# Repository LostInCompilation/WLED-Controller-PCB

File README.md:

# WLED Controller (ESP32) - 4 Channels - Current and power monitoring

### ❤️💰 Donation - Help a student pay rent

## You can buy the PCB in my shop
Buy the PCB here (available in 2 days): https://buymeacoffee.com/lostincompilation

## Features
- 4 Channels
    - Max 25A total
    - Max 10A per channel
- Every channel has _independent_ current, power and voltage monitoring (using INA219)
- Sending power monitoring data to HomeAssistant via MQTT
- Relay for cutting power to LED-strips
- Touch surface on PCB (next to LED) usable as custom button
- SMD-1206 parts for easy hand soldering
- Reverse polarity protection
- Seperate 3.3V low noise voltage regulator for audio section
- _**Optional:** INMP441 I2S Microphone with low noise power supply_
- _**Optional:** Line-In Audio with extension board (I2S ADC: PCM1808)_

## Usermod
This board requires a usermod for WLED for full support of all features including power monitoring.

_**NOTE:** The usermod is currently in development and will be uploaded to thtis repository._

## 3D Board view

## Board

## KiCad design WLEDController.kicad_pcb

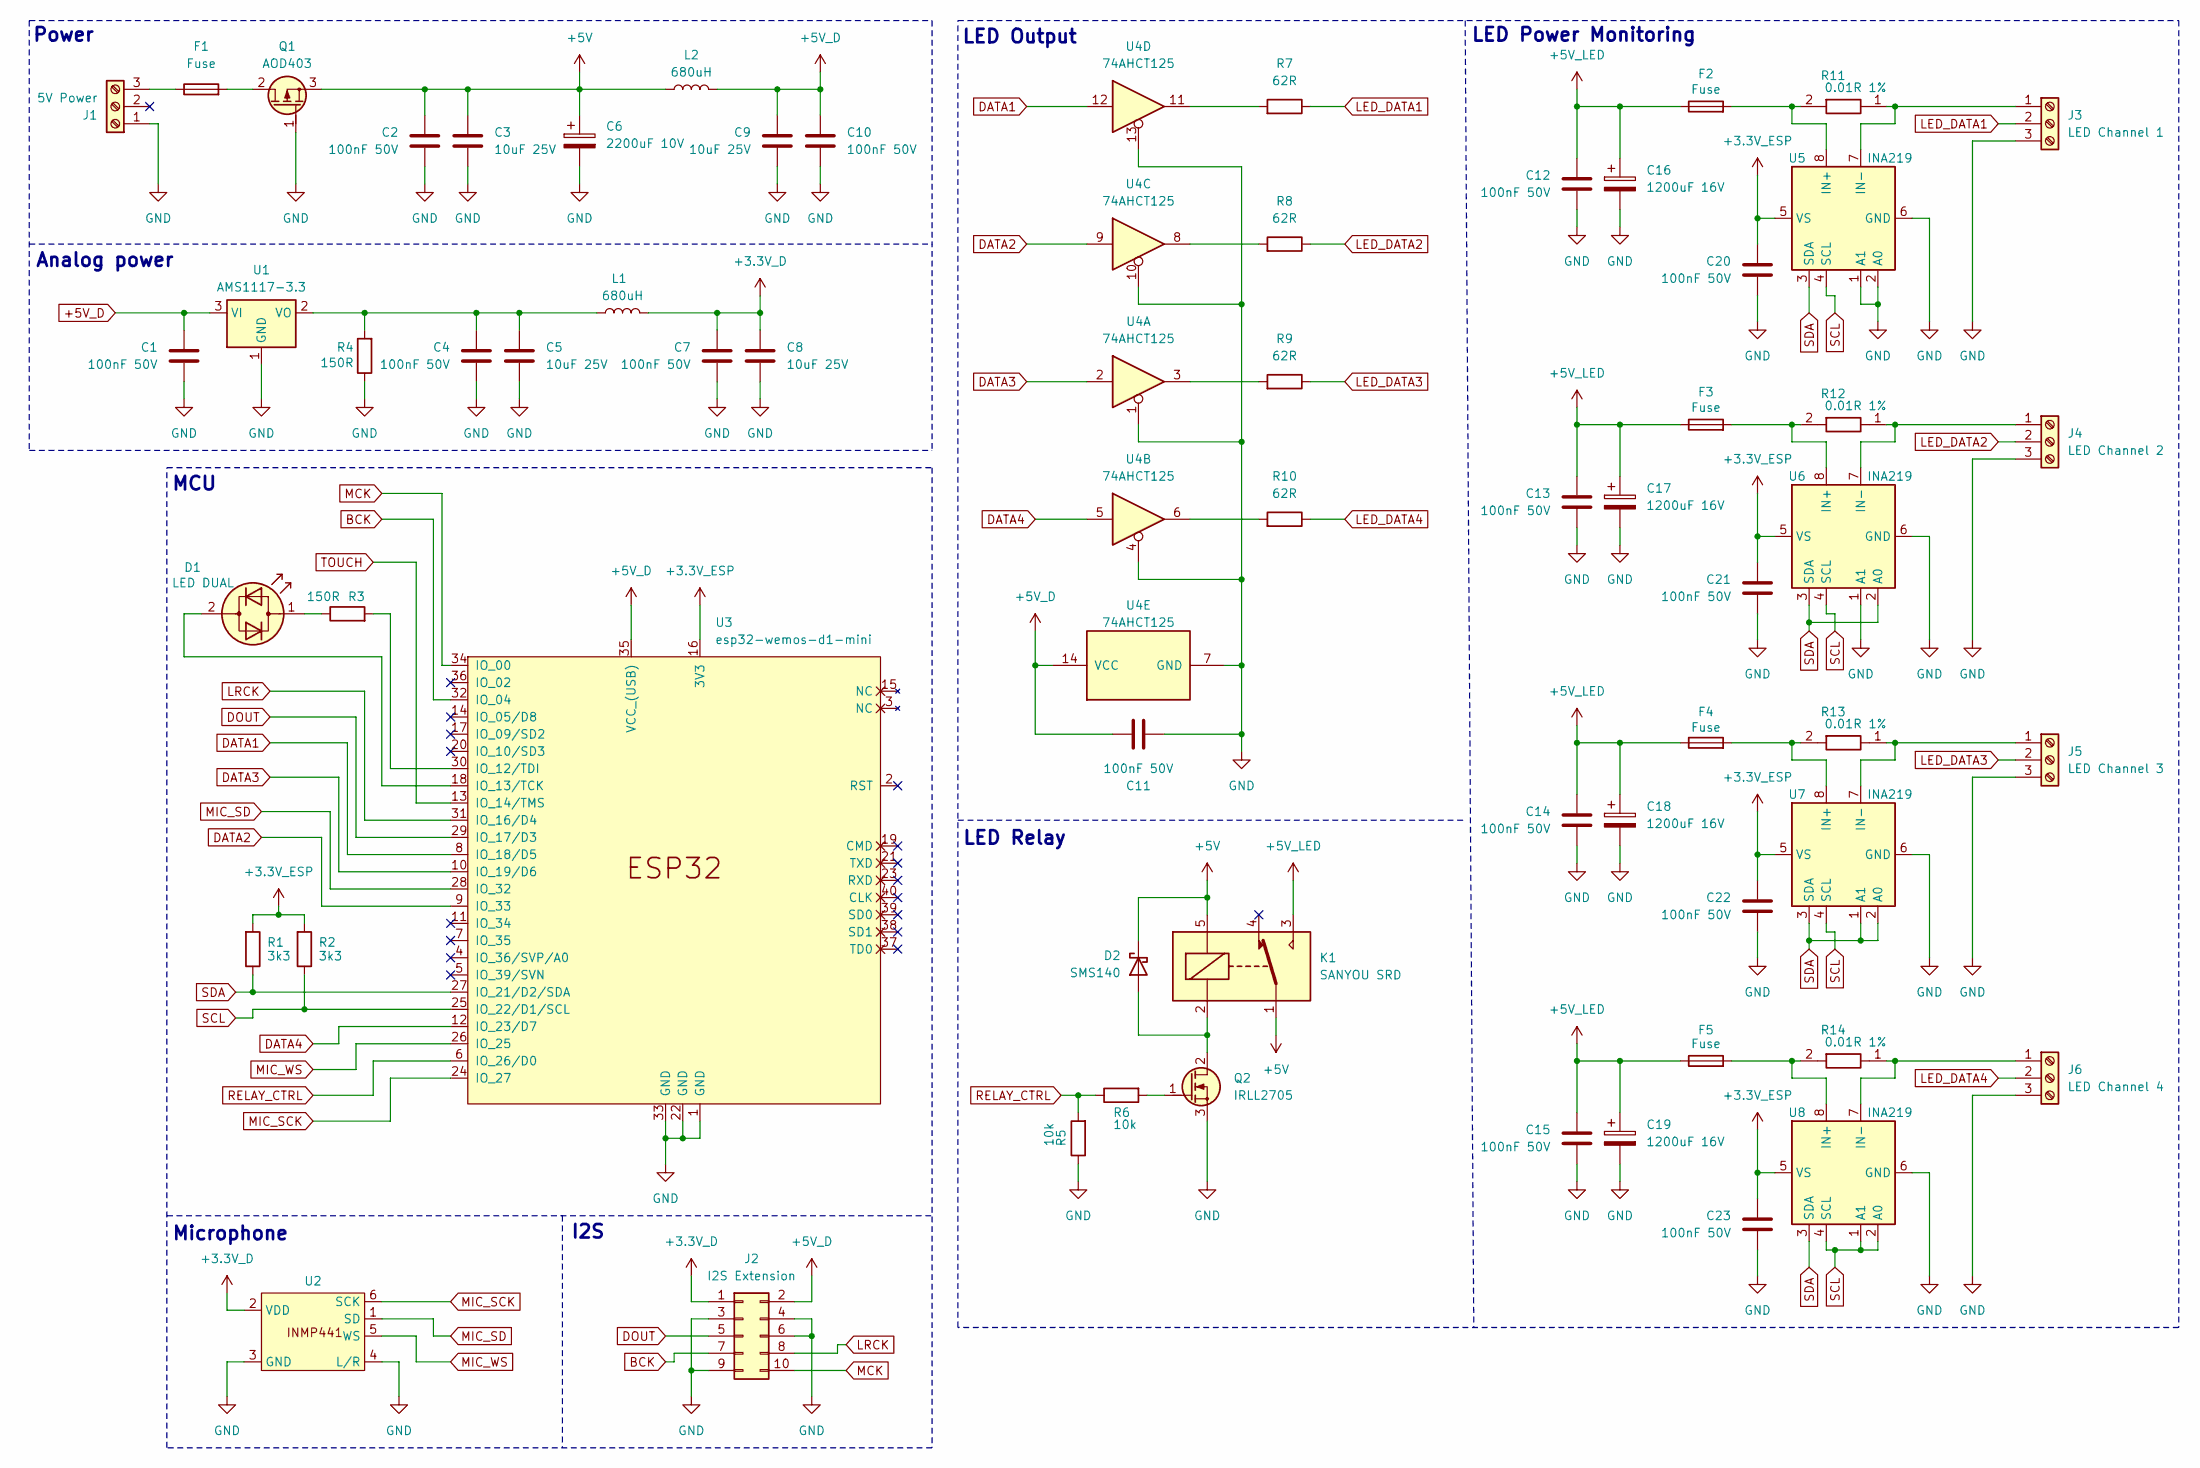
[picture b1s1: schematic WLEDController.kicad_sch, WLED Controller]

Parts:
C1, C2, C4, C7, C10, C11, C12, C13, C14, C15, C20, C21, C22, C23: 100nF 50V; C_1206_3216Metric
C3, C5, C8, C9: 10uF 25V; C_1206_3216Metric
C6: 2200uF 10V; CP_Radial_D10.0mm_P5.00mm
C16, C17, C18, C19: 1200uF 16V; CP_Radial_D10.0mm_P5.00mm
D1: LED DUAL; LED_D3.0mm_BiDir
D2: SMS140; D_MELF
F1, F2, F3, F4, F5: Fuse; Fuseholder_Littelfuse_Nano2_154x
J1: 5V Power; ScrewPlug_3P_Vertical
J2: I2S Extension; IDC-Header_2x05_P2.54mm_Horizontal
J3: LED Channel 1; ScrewPlug_3P_Vertical
J4: LED Channel 2; ScrewPlug_3P_Vertical
J5: LED Channel 3; ScrewPlug_3P_Vertical
J6: LED Channel 4; ScrewPlug_3P_Vertical
K1: SANYOU SRD; Relay_SPDT_SANYOU_SRD_Series_Form_C
L1, L2: 680uH; L_10.4x10.4_H4.8
Q1: AOD403; TO-252-2
Q2: IRLL2705; SOT-223-3_TabPin2
R1, R2: 3k3; R_1206_3216Metric
R3, R4: 150R; R_1206_3216Metric
R5, R6: 10k; R_1206_3216Metric
R7, R8, R9, R10: 62R; R_Axial_DIN0207_L6.3mm_D2.5mm_P10.16mm_Horizontal
R11, R12, R13, R14: 0.01R 1%; 2512_Shunt
U1: AMS1117-3.3; SOT-223-3_TabPin2
U2: INMP441_Module
U3: esp32-wemos-d1-mini
U4: 74AHCT125; TSSOP-14_4.4x5mm_P0.65mm
U5, U6, U7, U8: INA219; SOIC-8_3.9x4.9mm_P1.27mm

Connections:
+3.3V_D: C7.1, C8.1, J2.1, L1.2, U2.2 (VDD)
+3.3V_ESP: C20.1, C21.1, C22.1, C23.1, R1.1, R2.1, U3.16 (3V3), U5.5 (VS), U6.5 (VS), U7.5 (VS), U8.5 (VS)
+5V: C2.1, C3.1, C6.1, D2.1 (K), K1.1, K1.5, L2.1, Q1.3 (S)
+5V_D: C1.1, C9.1, C10.1, C11.2, J2.2, L2.2, U1.3 (VI), U3.35 (VCC_(USB)), U4.14 (VCC)
+5V_LED: C12.1, C13.1, C14.1, C15.1, C16.1, C17.1, C18.1, C19.1, F2.1, F3.1, F4.1, F5.1, K1.3
BCK: J2.7, U3.32 (IO_04)
DATA1: U3.8 (IO_18/D5), U4.12
DATA2: U3.9 (IO_33), U4.9
DATA3: U3.10 (IO_19/D6), U4.2
DATA4: U3.12 (IO_23/D7), U4.5
DOUT: J2.5, U3.29 (IO_17/D3)
GND: C1.2, C2.2, C3.2, C4.2, C5.2, C6.2, C7.2, C8.2, C9.2, C10.2, C11.1, C12.2, C13.2, C14.2, C15.2, C16.2, C17.2, C18.2, C19.2, C20.2, C21.2, C22.2, C23.2, J1.1, J2.3, J2.4, J2.6, J2.9, J3.3, J4.3, J5.3, J6.3, Q1.1 (G), Q2.3 (S), R4.2, R5.2, U1.1 (GND), U2.3 (GND), U2.4 (L/R), U3.1 (GND), U3.22 (GND), U3.33 (GND), U4.1, U4.4, U4.7 (GND), U4.10, U4.13, U5.1 (A1), U5.2 (A0), U5.6 (GND), U6.1 (A1), U6.6 (GND), U7.6 (GND), U8.6 (GND)
LED_DATA1: J3.2, R7.2
LED_DATA2: J4.2, R8.2
LED_DATA3: J5.2, R9.2
LED_DATA4: J6.2, R10.2
LRCK: J2.8, U3.31 (IO_16/D4)
MCK: J2.10, U3.34 (IO_00)
MIC_SCK: U2.6 (SCK), U3.24 (IO_27)
MIC_SD: U2.1 (SD), U3.28 (IO_32)
MIC_WS: U2.5 (WS), U3.26 (IO_25)
unnamed: D1.2 (AK), U3.18 (IO_13/TCK)
unnamed: D1.1 (KA), R3.2
unnamed: D2.2 (A), K1.2, Q2.2 (D)
unnamed: F1.1, J1.3
unnamed: J3.1, R11.1, U5.7 (IN-)
unnamed: J4.1, R12.1, U6.7 (IN-)
unnamed: J5.1, R13.1, U7.7 (IN-)
unnamed: J6.1, R14.1, U8.7 (IN-)
unnamed: F1.2, Q1.2 (D)
unnamed: Q2.1 (G), R6.1
unnamed: R7.1, U4.11
unnamed: R8.1, U4.8
unnamed: R9.1, U4.3
unnamed: R10.1, U4.6
unnamed: C4.1, C5.1, L1.1, R4.1, U1.2 (VO)
unnamed: R3.1, U3.30 (IO_12/TDI)
unnamed: F2.2, R11.2, U5.8 (IN+)
unnamed: F3.2, R12.2, U6.8 (IN+)
unnamed: F4.2, R13.2, U7.8 (IN+)
unnamed: F5.2, R14.2, U8.8 (IN+)
RELAY_CTRL: R5.1, R6.2, U3.6 (IO_26/D0)
SCL: R2.2, U3.25 (IO_22/D1/SCL), U5.4 (SCL), U6.4 (SCL), U7.4 (SCL), U8.1 (A1), U8.2 (A0), U8.4 (SCL)
SDA: R1.2, U3.27 (IO_21/D2/SDA), U5.3 (SDA), U6.2 (A0), U6.3 (SDA), U7.1 (A1), U7.2 (A0), U7.3 (SDA), U8.3 (SDA)
TOUCH: U3.13 (IO_14/TMS)

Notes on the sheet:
I2S
LED Relay
Analog power
Power
MCU
LED Power Monitoring
LED Output
Microphone

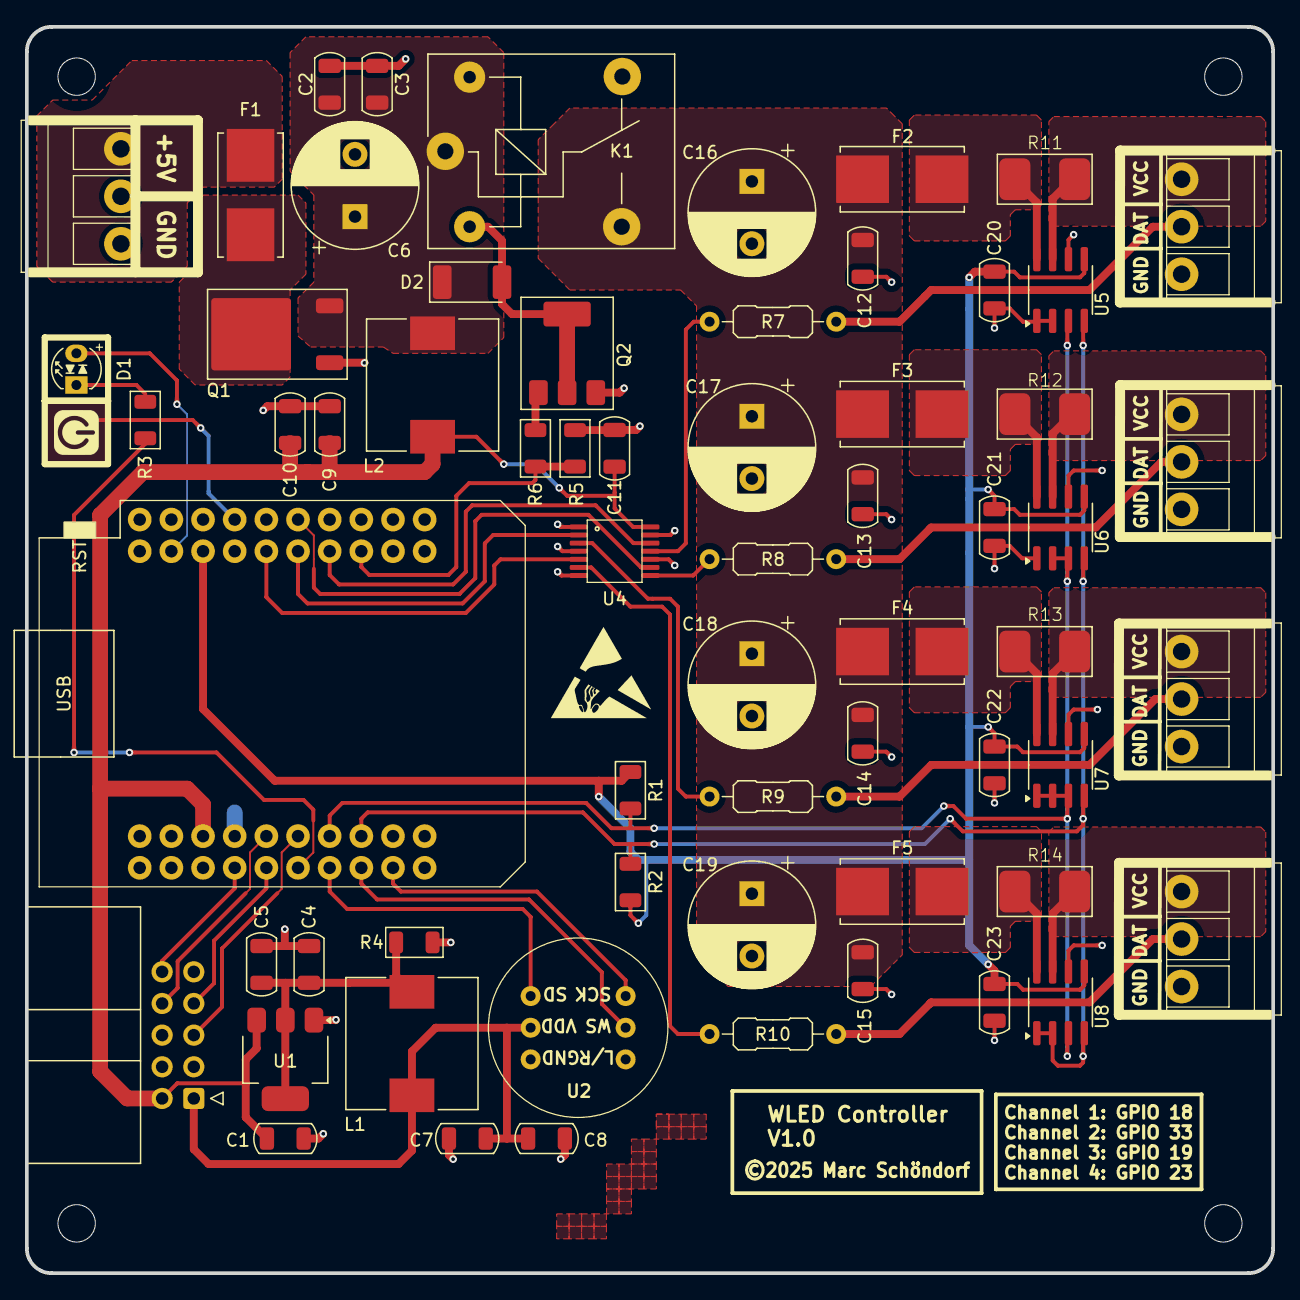
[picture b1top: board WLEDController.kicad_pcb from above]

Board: 2 copper layers, 100.0 x 100.0 mm, 63 parts (0 on the bottom side), 44 nets.

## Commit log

2025-02-03 Cleanup
2025-02-03 Added Gerber
2025-02-03 Update file structure
2025-02-03 Added Touch sensor
2025-02-03 Gerber zip
2025-02-03 Added old version for archival purposes

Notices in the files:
WLEDController.kicad_pcb:
©2025 Marc Schöndorf
